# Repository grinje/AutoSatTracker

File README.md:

# AutoSatTracker-ESP32
Tracking satellites with custom hardware based on stepper motors. A blog description of the project can be found at https://www.la3t.no/automatic-satellite-tracker/

The construction of the rotator is based on the SatNOGS project found here: https://gitlab.com/librespacefoundation/satnogs/satnogs-rotator/tree/master

The controller is based on the work by Elwood Downey found here: http://clearskyinstitute.com/ham/AST/. 
The software is based on this repo by Bjoern Kerler: https://github.com/bkerler/AutoSatTracker-ESP

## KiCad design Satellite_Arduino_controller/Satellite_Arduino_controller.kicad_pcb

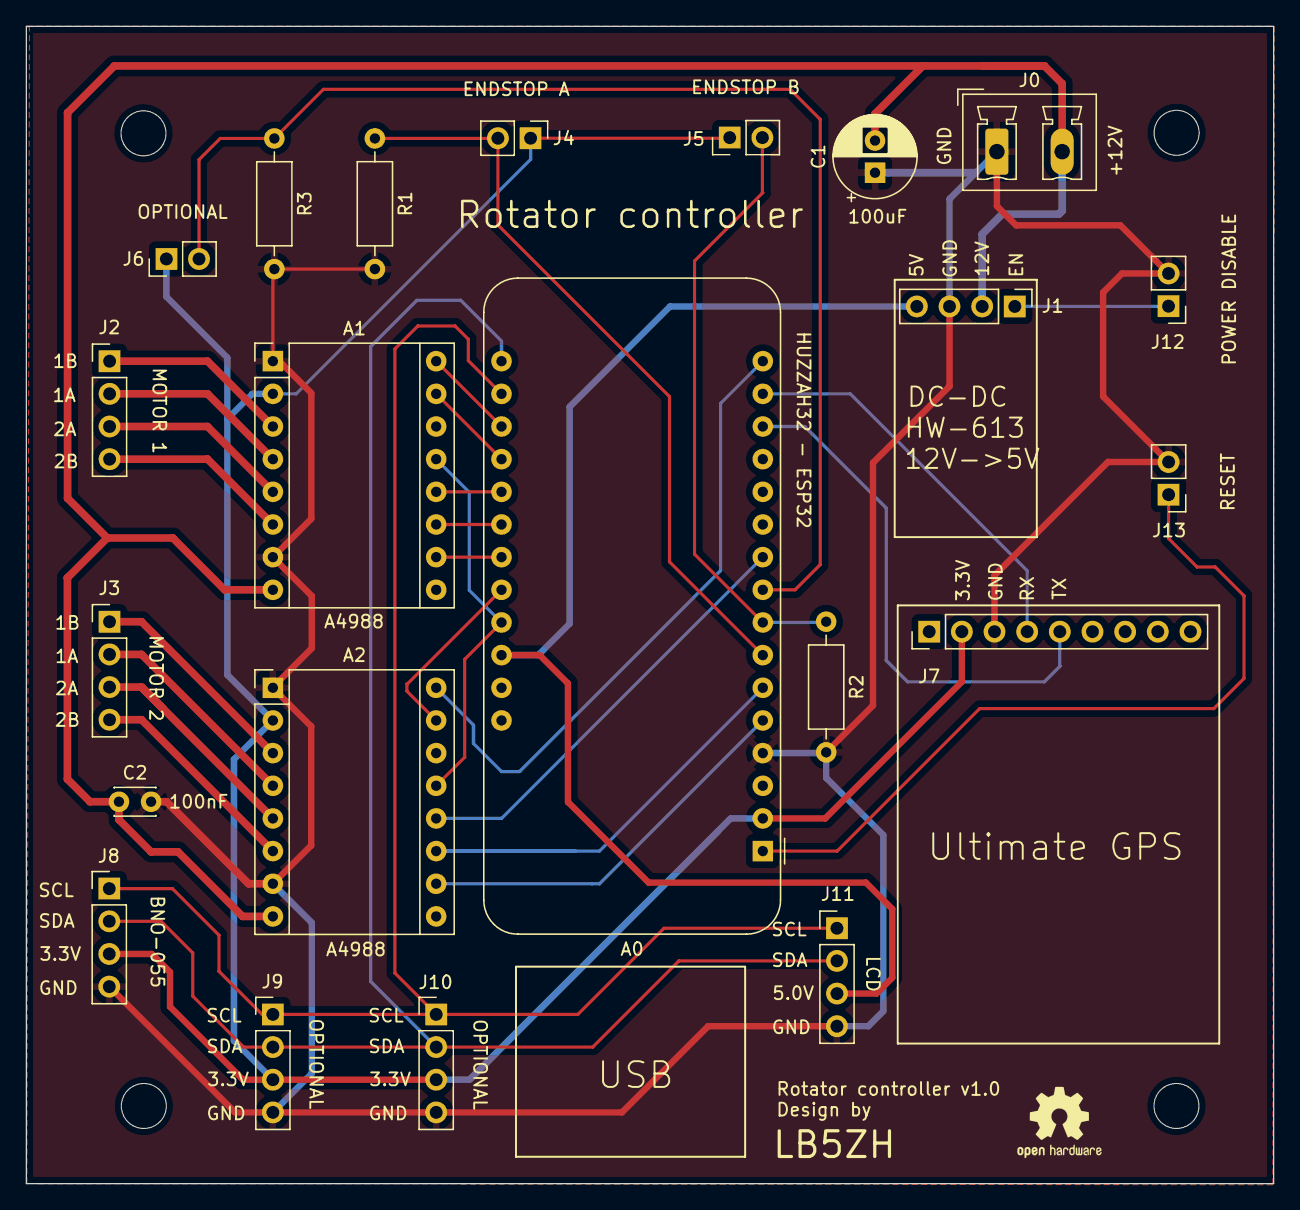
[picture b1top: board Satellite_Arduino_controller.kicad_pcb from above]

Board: 2 copper layers, 97.0 x 90.0 mm, 22 parts (0 on the bottom side), 32 nets.

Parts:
A0: Adafruit_Feather_HUZZAH32_ESP32; Adafruit_Feather
A1, A2: A4988; Pololu_Breakout-16_15.2x20.3mm
C1: 100uF; CP_Radial_D6.3mm_P2.50mm
C2: 100nF; C_Disc_D3.0mm_W2.0mm_P2.50mm
J0: Power input; PhoenixContact_MCV_1,5_2-G-5.08_1x02_P5.08mm_Vertical
J1: DC-DC; PinHeader_1x04_P2.54mm_Vertical
J2: Motor 1; PinHeader_1x04_P2.54mm_Vertical
J3: Motor 2; PinHeader_1x04_P2.54mm_Vertical
J4: Endstop A; PinHeader_1x02_P2.54mm_Vertical
J5: Endstop B; PinHeader_1x02_P2.54mm_Vertical
J6: Optional; PinHeader_1x02_P2.54mm_Vertical
J7: Ultimate GPS; PinHeader_1x09_P2.54mm_Vertical
J8: BNO-055; PinHeader_1x04_P2.54mm_Vertical
J9, J10: Optional sensor; PinHeader_1x04_P2.54mm_Vertical
J11: LCD 20x4; PinHeader_1x04_P2.54mm_Vertical
J12: Power disable; PinHeader_1x02_P2.54mm_Vertical
J13: RESET; PinHeader_1x02_P2.54mm_Vertical
R1, R2, R3: 10k; R_Axial_DIN0207_L6.3mm_D2.5mm_P10.16mm_Horizontal

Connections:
+3V3: A0.2 (3V3), A1.2 (VDD), A2.2 (VDD), J4.1, J5.1, J6.1, J7.2, J8.3, J9.3, J10.3
+5V: A0.26 (USB), J1.4, J11.3
+12V: A1.8 (VMOT), A2.8 (VMOT), C1.2, C2.1, J0.2, J1.2
/EN1: J1.1, J12.1
/RX: A0.15 (TX/IO17), J7.4
/SCL: A0.18 (SCL/IO22), J8.1, J9.1, J10.1, J11.1
/SDA: A0.17 (SDA/IO23), J8.2, J9.2, J10.2, J11.2
/TX: A0.14 (RX/IO16), J7.5
GND: A0.4 (GND), A1.1 (GND), A1.7 (GND), A2.1 (GND), A2.7 (GND), C1.1, C2.2, J0.1, J1.3, J7.3, J8.4, J9.4, J10.4, J11.4, J12.2, J13.2, R1.2, R2.2, R3.2
unnamed: A0.1 (~RESET), J13.1
unnamed: A0.5 (DAC2/A0), A2.10 (MS1)
unnamed: A0.6 (DAC1/A1), A2.11 (MS2)
unnamed: A0.7 (I34/A2), J4.2, R1.1
unnamed: A0.8 (I39/A3), J5.2, R2.1
unnamed: A0.9 (IO36/A4), J6.2, R3.1
unnamed: A0.10 (IO4/A5), A2.12 (MS3)
unnamed: A0.16 (IO21), A2.16 (DIR)
unnamed: A0.19 (A6/IO14), A1.16 (DIR)
unnamed: A0.20 (A7/IO32), A1.15 (STEP)
unnamed: A0.21 (A8/IO15), A1.12 (MS3)
unnamed: A0.22 (A9/IO33), A1.11 (MS2)
unnamed: A0.23 (A10/IO27), A1.10 (MS1)
unnamed: A0.24 (A11/IO12), A2.15 (STEP)
unnamed: A0.25 (A12/IO13), A1.13 (~RESET), A2.13 (~RESET)
unnamed: A1.3 (1B), J2.1
unnamed: A1.4 (1A), J2.2
unnamed: A1.5 (2A), J2.3
unnamed: A1.6 (2B), J2.4
unnamed: A2.3 (1B), J3.1
unnamed: A2.4 (1A), J3.2
unnamed: A2.5 (2A), J3.3
unnamed: A2.6 (2B), J3.4

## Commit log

2021-03-30 Moved things around
2021-03-30 Renamed dir
2021-04-20 Updated LCD class
2021-04-20 Updated magdecl
2021-10-06 Delivered version
2021-10-06 Added schema and pcb
2021-10-06 Added CAD files
